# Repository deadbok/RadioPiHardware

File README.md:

RadioPi Hardware
================

These are the files for the DIY hardware used in the RadioPi.
It is an I2C expander used to connect the HD44780 LCD and the controls to the Raspberry Pi.

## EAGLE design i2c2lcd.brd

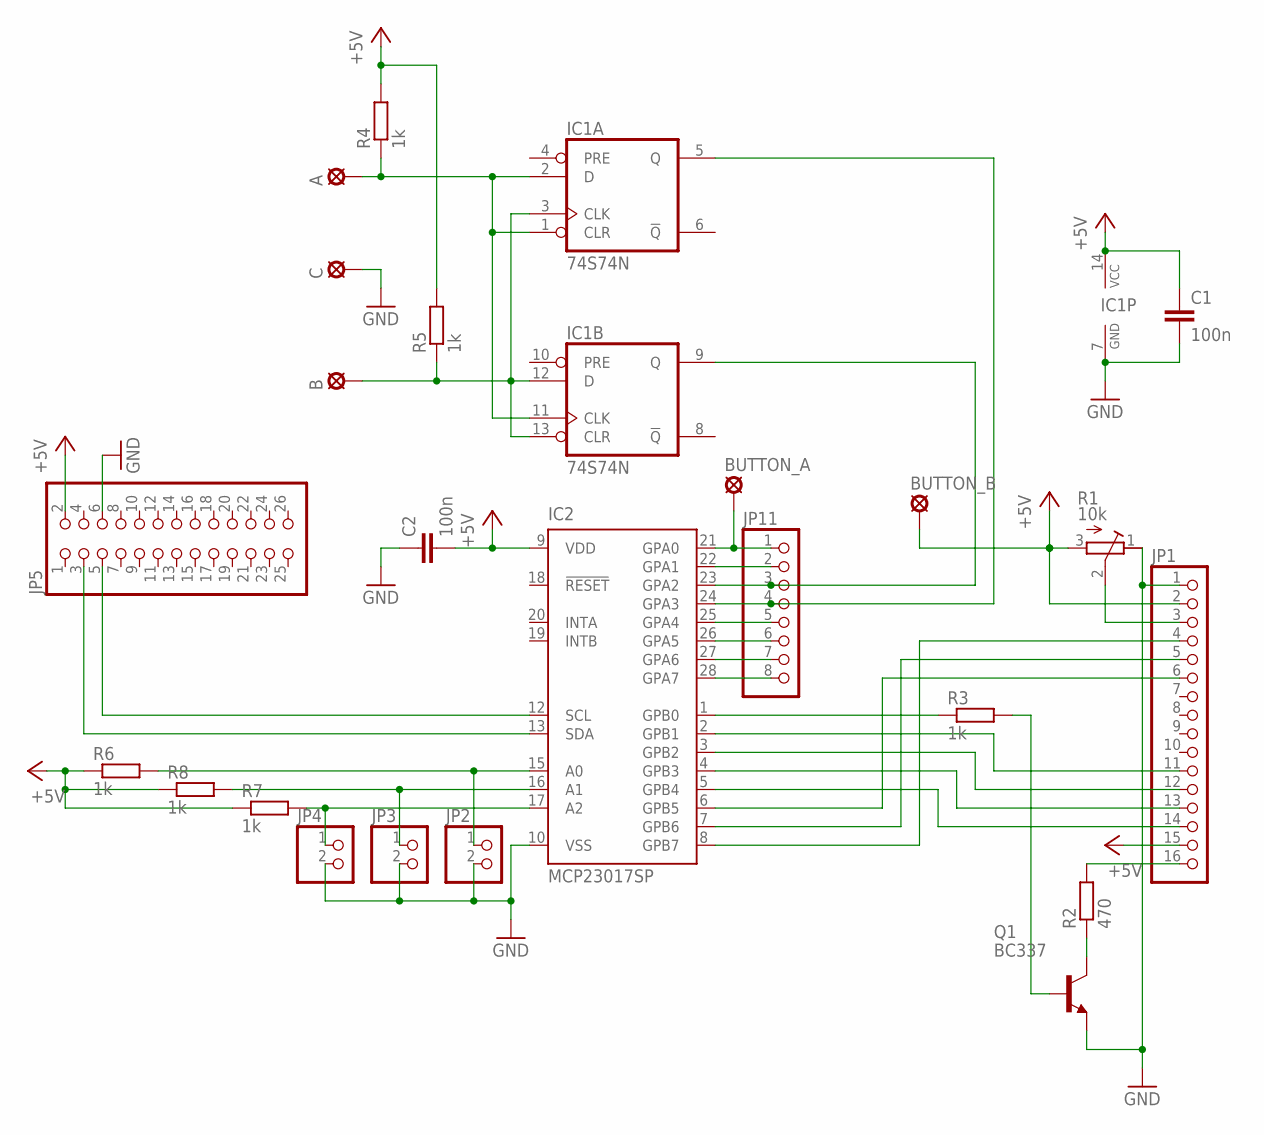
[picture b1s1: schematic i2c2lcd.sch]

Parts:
A: LSP13
B: LSP13
BUTTON_A: LSP13
BUTTON_B: LSP13
C: LSP13
C1, C2: 100n; C1206K
IC1: 74S74N; DIL14
IC2: MCP23017SP; DIL28-3
JP1: PINHD-1X16; 1X16
JP2, JP3, JP4: PINHD-1X2; 1X02
JP5: PINHD-2X13; 2X13
JP11: PINHD-1X8; 1X08
Q1: BC337; TO92
R1: 10k; RTRIM3006P
R2: 470; 0207/10
R3: 1k; 0207/12
R4, R5, R6, R7, R8: 1k; 0207/10

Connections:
+5V: BUTTON_B.MP, C1.1, C2.2, IC1.14 (VCC), IC2.9 (VDD), JP1.2, JP1.15, JP5.2, R1.3 (A), R4.2, R5.2, R6.1, R7.1, R8.1
GND: C.MP, C1.2, C2.1, IC1.7 (GND), IC2.10 (VSS), JP1.1, JP2.2, JP3.2, JP4.2, JP5.6, Q1.1 (E), R1.1 (E)
unnamed: JP1.3, R1.2 (S)
unnamed: IC2.8 (GPB7), JP1.4
unnamed: IC2.7 (GPB6), JP1.5
unnamed: IC2.22 (GPA1), JP11.2
unnamed: IC2.5 (GPB4), JP1.14
unnamed: IC2.4 (GPB3), JP1.13
unnamed: IC2.3 (GPB2), JP1.12
unnamed: IC2.2 (GPB1), JP1.11
unnamed: JP1.16, R2.2
unnamed: Q1.3 (C), R2.1
unnamed: Q1.2 (B), R3.2
unnamed: IC2.1 (GPB0), R3.1
unnamed: IC2.15 (A0), JP2.1, R6.2
unnamed: B.MP, IC1.3 (CLK), IC1.12 (D), IC1.13 (CLR), R5.1
unnamed: IC2.16 (A1), JP3.1, R8.2
unnamed: IC2.17 (A2), JP4.1, R7.2
unnamed: IC1.5 (Q), IC2.24 (GPA3), JP11.4
unnamed: IC1.9 (Q), IC2.23 (GPA2), JP11.3
unnamed: IC2.6 (GPB5), JP1.6
unnamed: BUTTON_A.MP, IC2.21 (GPA0), JP11.1
unnamed: IC2.13 (SDA), JP5.3
unnamed: IC2.12 (SCL), JP5.5
unnamed: IC2.25 (GPA4), JP11.5
unnamed: IC2.26 (GPA5), JP11.6
unnamed: IC2.27 (GPA6), JP11.7
unnamed: IC2.28 (GPA7), JP11.8
unnamed: A.MP, IC1.1 (CLR), IC1.2 (D), IC1.11 (CLK), R4.1

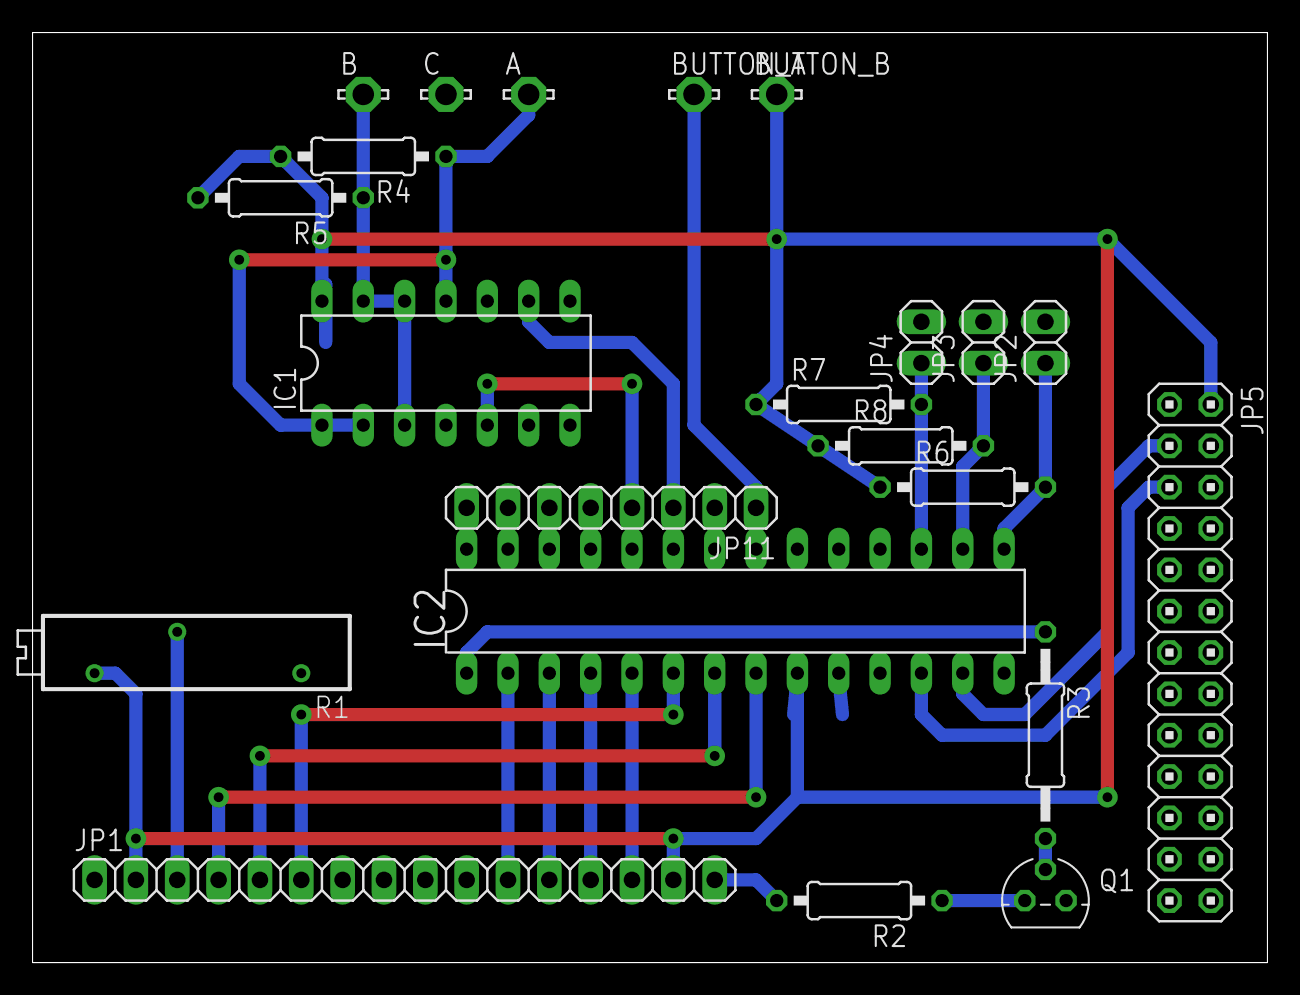
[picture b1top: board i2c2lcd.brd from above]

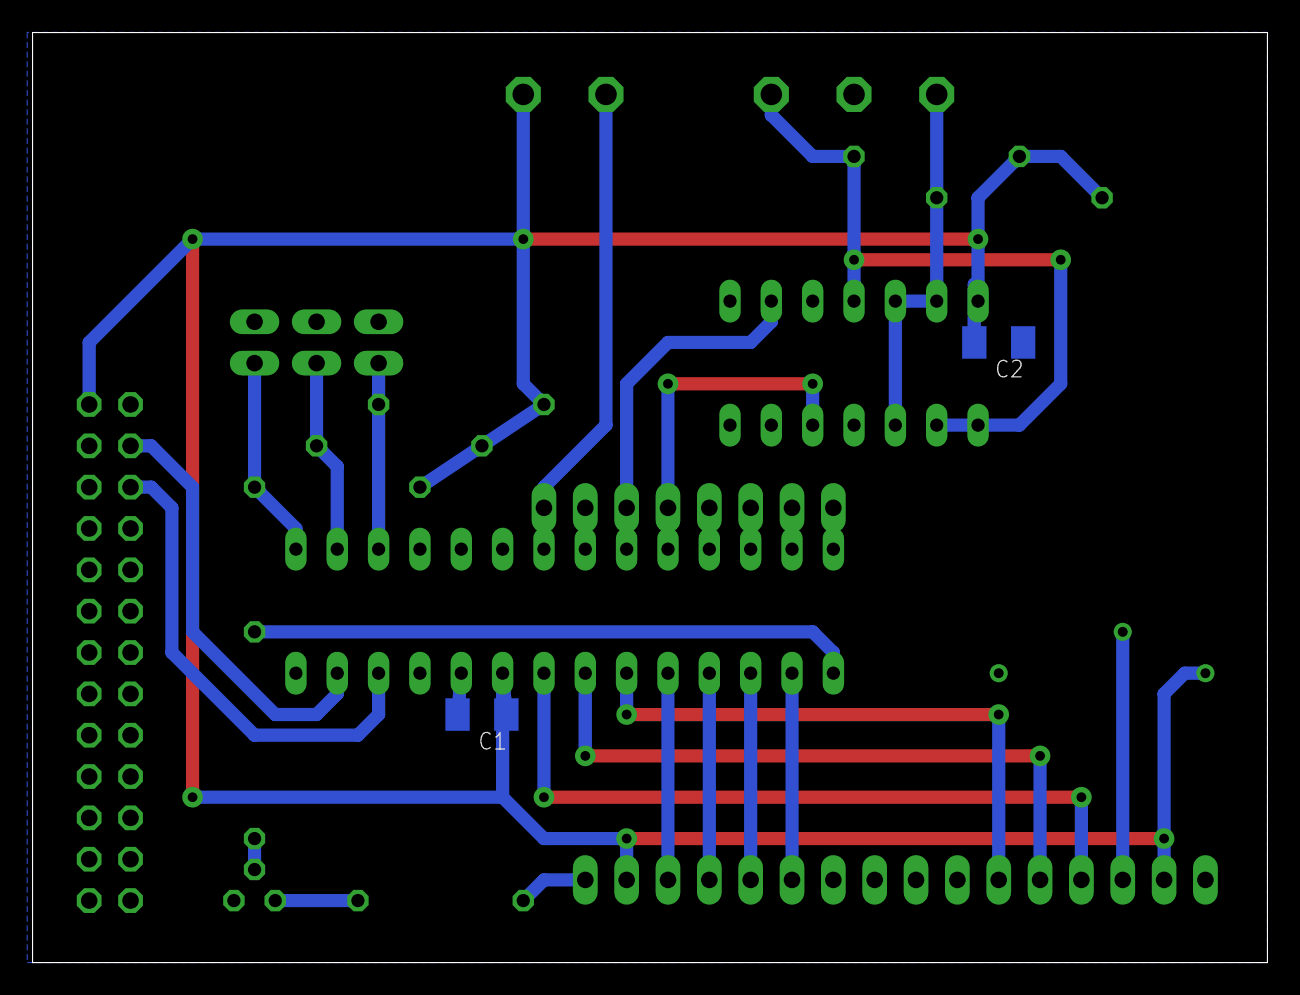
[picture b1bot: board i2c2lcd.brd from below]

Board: 2 copper layers, 75.9 x 57.1 mm, 24 parts (2 on the bottom side), 29 nets.

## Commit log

2014-03-19 Initial commit.
